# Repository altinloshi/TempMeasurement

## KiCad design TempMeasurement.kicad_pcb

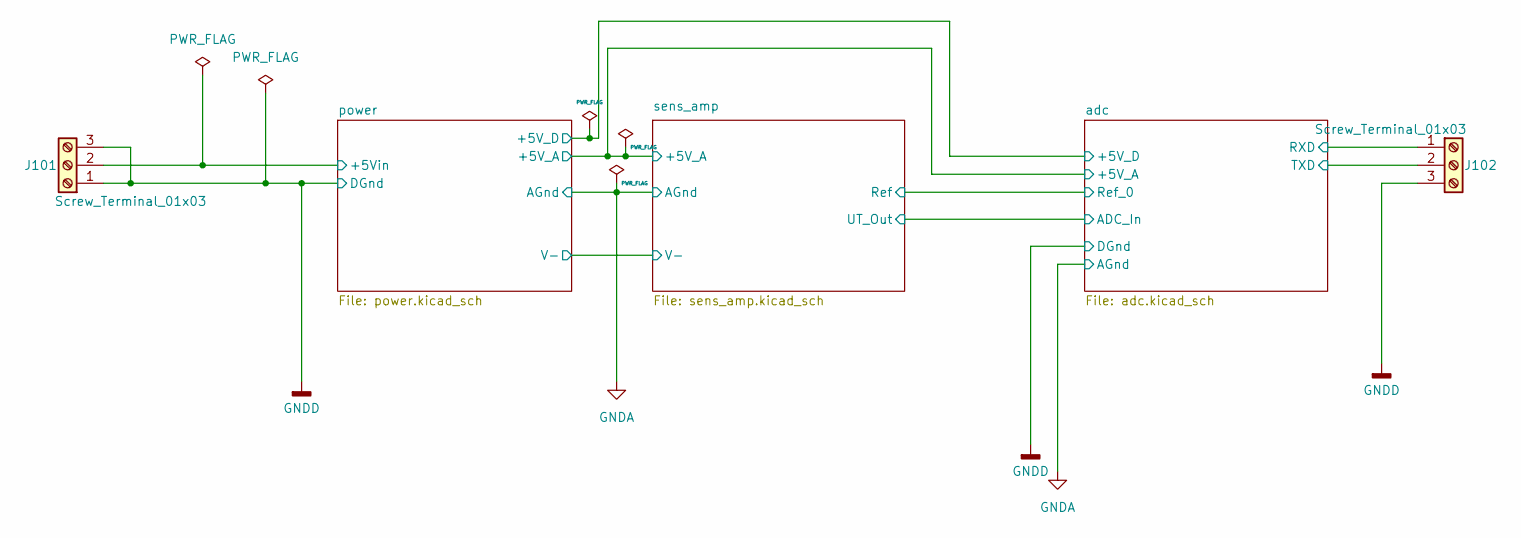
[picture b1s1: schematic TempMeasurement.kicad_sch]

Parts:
J101, J102: Screw_Terminal_01x03; TerminalBlock_Phoenix_MPT-0,5-3-2.54_1x03_P2.54mm_Horizontal

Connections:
/adc/RXD: J102.1; also elsewhere on the board
/adc/TXD: J102.2; also elsewhere on the board
/power/+5Vin: J101.2; also elsewhere on the board
GNDD: J101.1, J101.3, J102.3; also elsewhere on the board

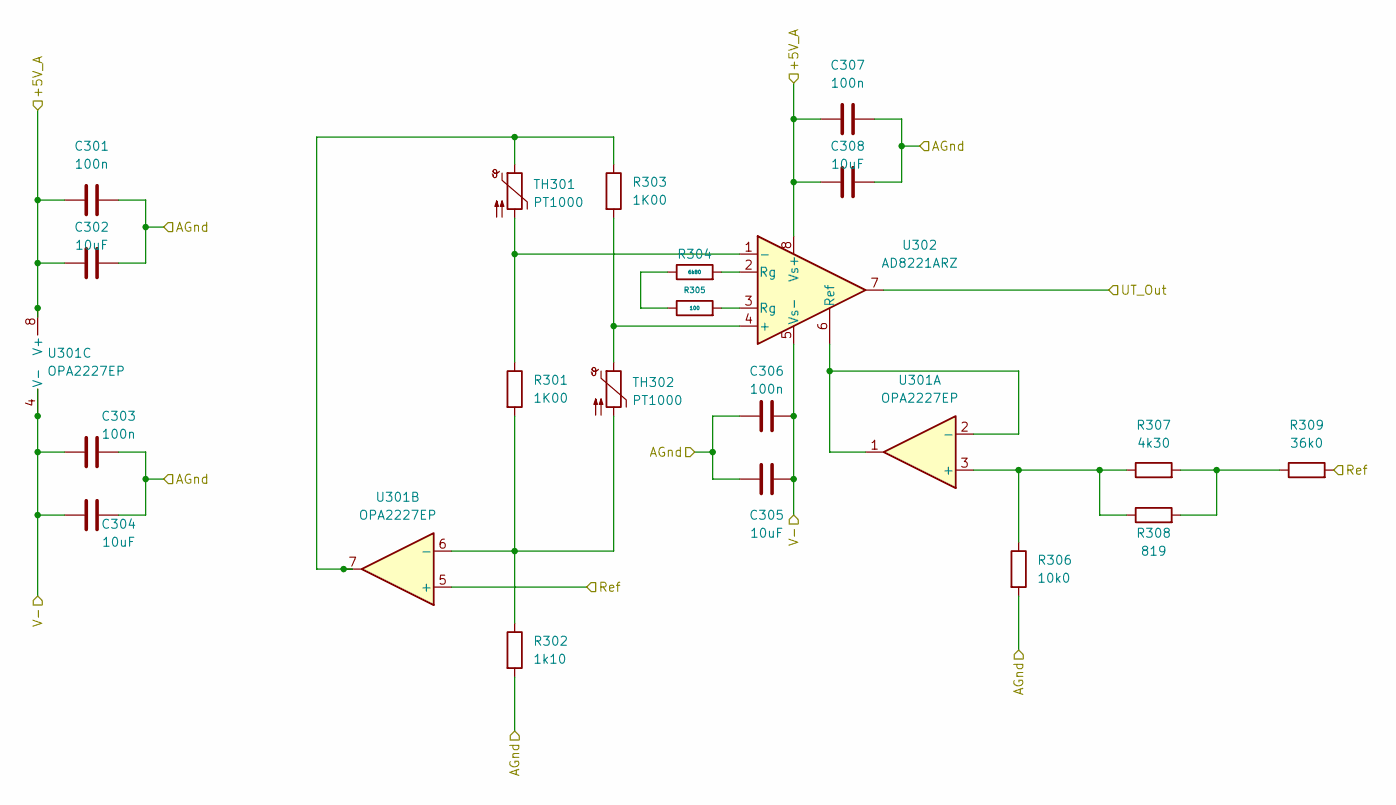
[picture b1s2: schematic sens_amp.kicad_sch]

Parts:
C301, C303, C305, C307: 100n; C_0805_2012Metric
C302, C304, C306, C308: 10uF; C_0805_2012Metric
R301, R303: 1K00; R_0805_2012Metric
R302: 1k10; R_0805_2012Metric
R304: 6k80; R_0805_2012Metric
R305: 100; R_0805_2012Metric
R306: 10k0; R_0805_2012Metric
R307: 4k30; R_0805_2012Metric
R308: 819; R_0805_2012Metric
R309: 36k0; R_0805_2012Metric
TH301, TH302: PT1000; R_0805_2012Metric
U301: OPA2227EP; SOIC-8_3.9x4.9mm_P1.27mm
U302: AD8221ARZ; SOIC-8_3.9x4.9mm_P1.27mm

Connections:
/adc/+5V_A: C301.1, C302.1, C307.1, C308.1, U301.8 (V+), U302.8 (Vs+); also elsewhere on the board
/adc/ADC_In: U302.7; also elsewhere on the board
/adc/Ref_0: R309.2, U301.5 (+); also elsewhere on the board
/power/V-: C303.1, C304.1, C305.1, C306.1, U301.4 (V-), U302.5 (Vs-); also elsewhere on the board
GNDA: C301.2, C302.2, C303.2, C304.2, C305.2, C306.2, C307.2, C308.2, R302.2, R306.2; also elsewhere on the board
unnamed: R303.1, TH301.1, U301.7
unnamed: R304.1, R305.1
unnamed: R304.2, U302.2 (Rg)
unnamed: R305.2, U302.3 (Rg)
unnamed: R307.2, R308.2, R309.1
unnamed: R306.1, R307.1, R308.1, U301.3 (+)
unnamed: U301.1, U301.2 (-), U302.6 (Ref)
unnamed: R301.2, R302.1, TH302.2, U301.6 (-)
unnamed: R303.2, TH302.1, U302.4 (+)
unnamed: R301.1, TH301.2, U302.1 (-)

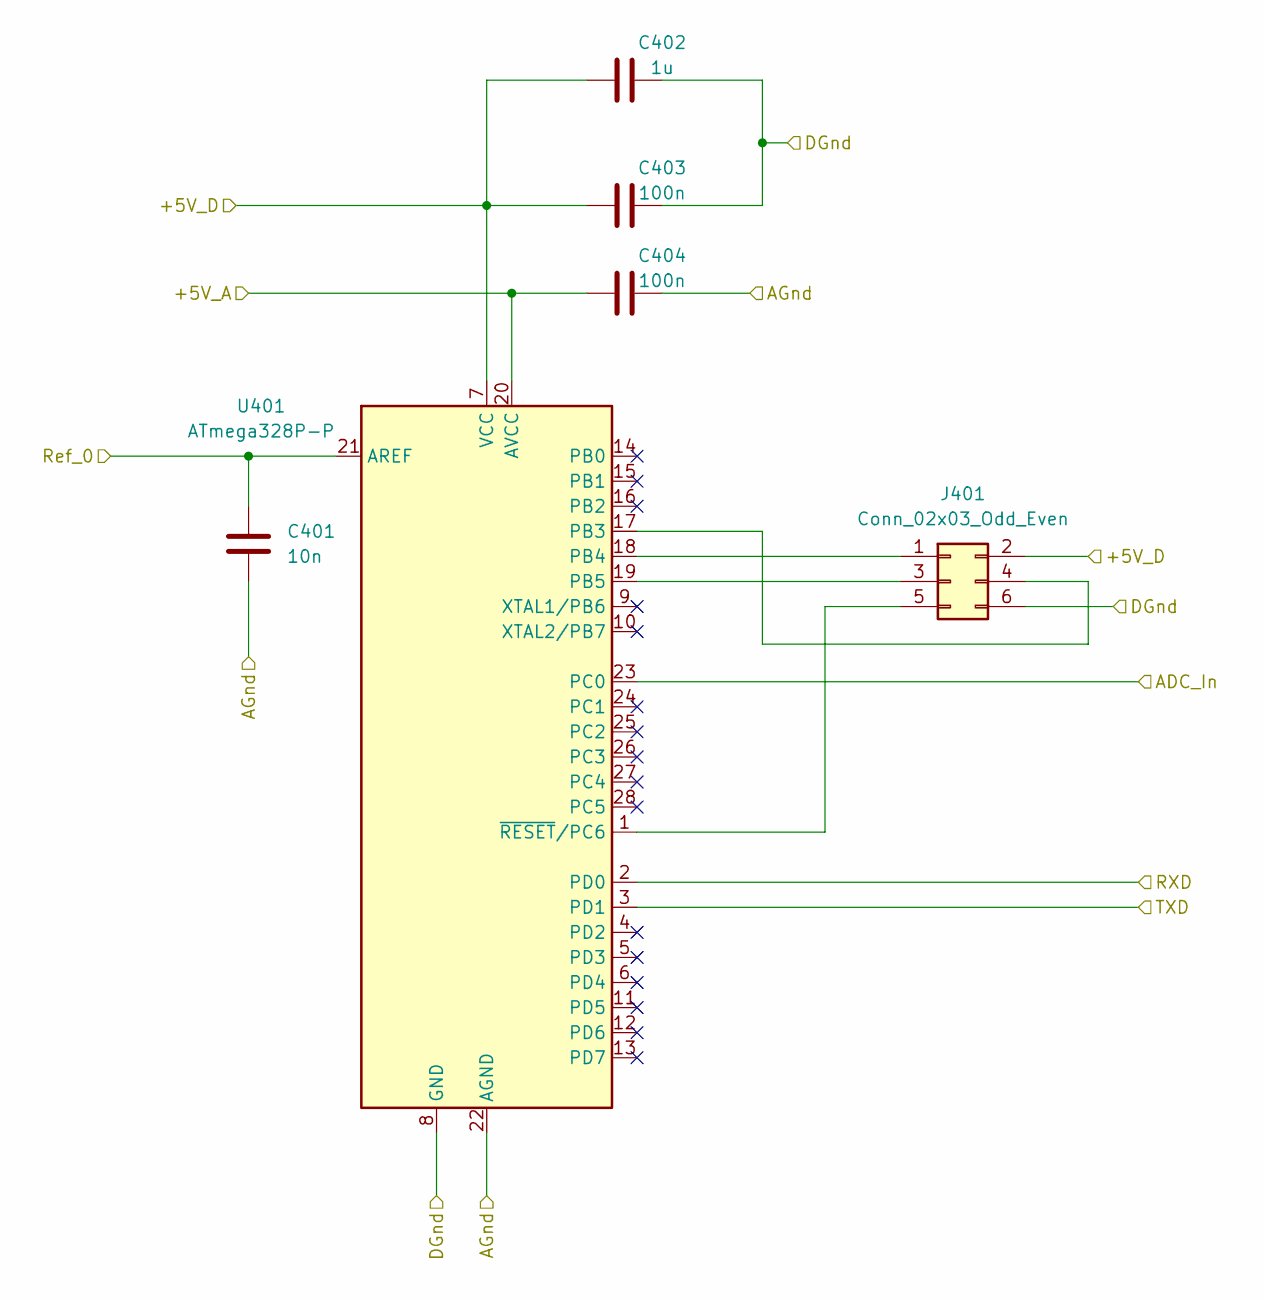
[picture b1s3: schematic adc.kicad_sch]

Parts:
C401: 10n; C_0805_2012Metric
C402: 1u; C_0805_2012Metric
C403, C404: 100n; C_0805_2012Metric
J401: Conn_02x03_Odd_Even; PinHeader_2x03_P2.54mm_Vertical
U401: ATmega328P-P; DIP-28_W7.62mm

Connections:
/adc/+5V_A: C404.1, U401.20 (AVCC); also elsewhere on the board
/adc/+5V_D: C402.1, C403.1, J401.2, U401.7 (VCC); also elsewhere on the board
/adc/ADC_In: U401.23 (PC0); also elsewhere on the board
/adc/RXD: U401.2 (PD0); also elsewhere on the board
/adc/Ref_0: C401.1, U401.21 (AREF); also elsewhere on the board
/adc/TXD: U401.3 (PD1); also elsewhere on the board
GNDA: C401.2, C404.2, U401.22 (AGND); also elsewhere on the board
GNDD: C402.2, C403.2, J401.6, U401.8 (GND); also elsewhere on the board
unnamed: J401.1, U401.18 (PB4)
unnamed: J401.3, U401.19 (PB5)
unnamed: J401.4, U401.17 (PB3)
unnamed: J401.5, U401.1 (~RESET/PC6)

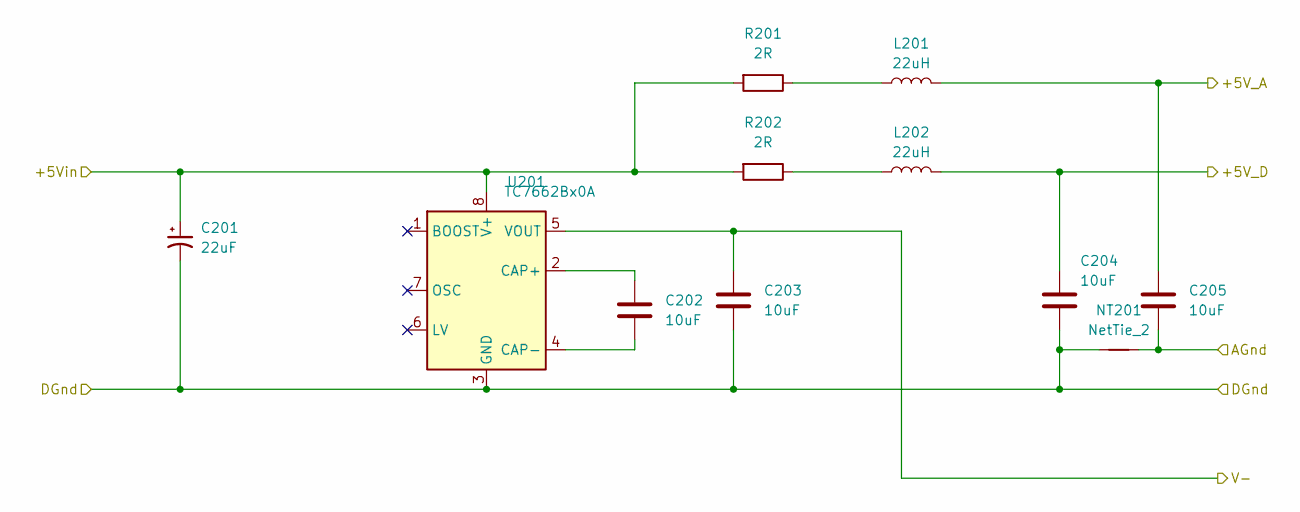
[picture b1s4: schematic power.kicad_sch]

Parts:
C201: 22uF; CP_EIA-7343-15_Kemet-W
C202, C203, C204, C205: 10uF; C_0805_2012Metric
L201, L202: 22uH; L_0805_2012Metric
NT201: NetTie_2; NetTie-2_SMD_Pad2.0mm
R201, R202: 2R; R_0805_2012Metric
U201: TC7662Bx0A; SOIC-8_3.9x4.9mm_P1.27mm

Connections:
/adc/+5V_A: C205.1, L201.2; also elsewhere on the board
/adc/+5V_D: C204.1, L202.2; also elsewhere on the board
/power/+5Vin: C201.1, R201.2, R202.2, U201.8 (V+); also elsewhere on the board
/power/V-: C203.1, U201.5 (VOUT); also elsewhere on the board
GNDA: C205.2, NT201.2; also elsewhere on the board
GNDD: C201.2, C203.2, C204.2, NT201.1, U201.3 (GND); also elsewhere on the board
unnamed: L201.1, R201.1
unnamed: L202.1, R202.1
unnamed: C202.1, U201.2 (CAP+)
unnamed: C202.2, U201.4 (CAP-)

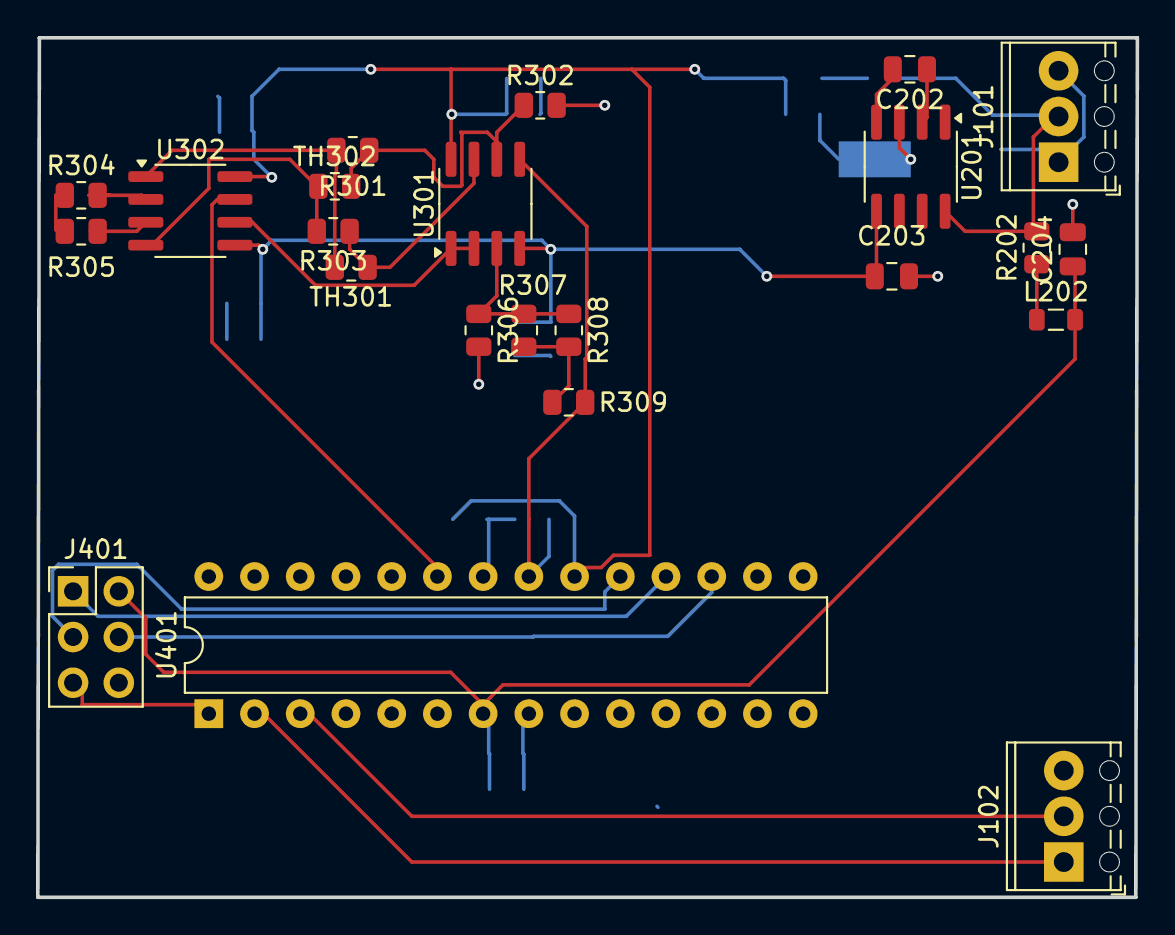
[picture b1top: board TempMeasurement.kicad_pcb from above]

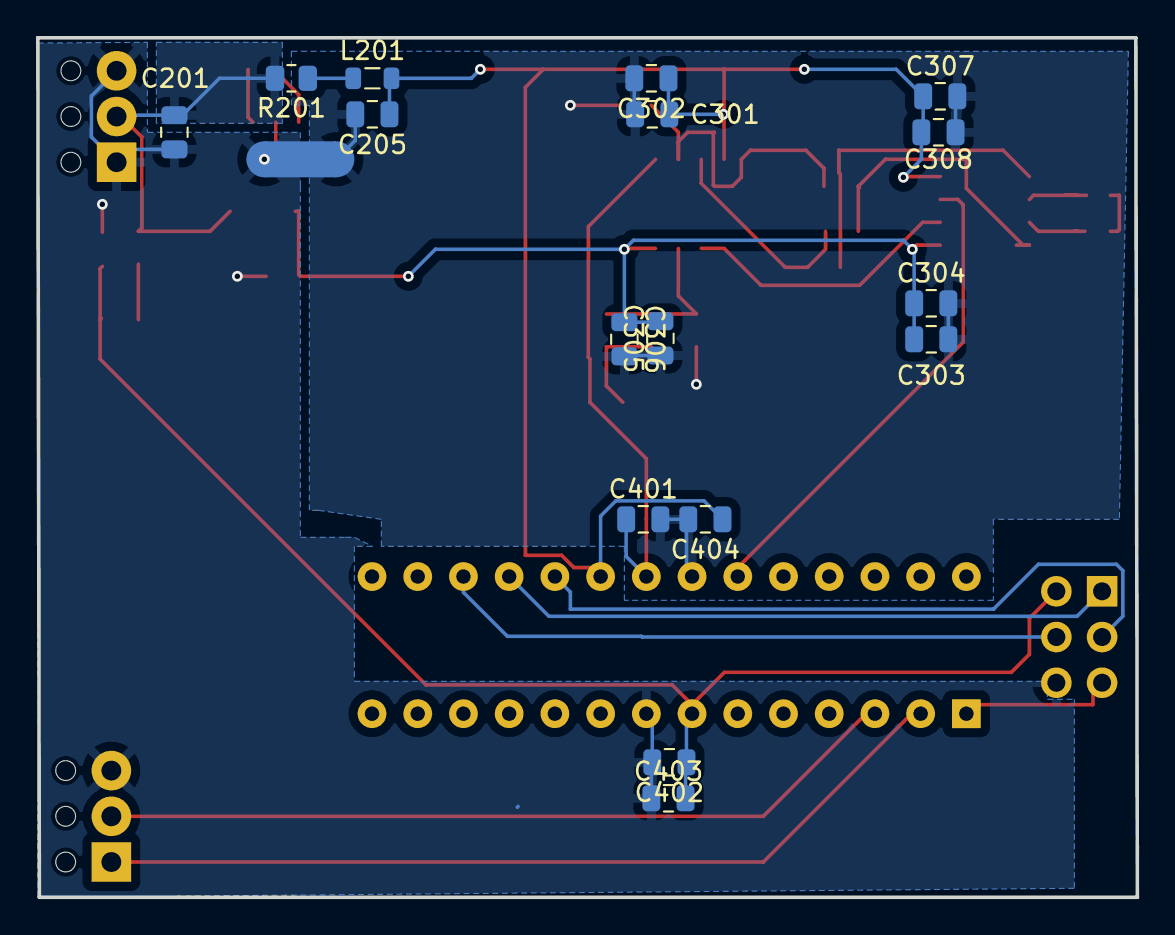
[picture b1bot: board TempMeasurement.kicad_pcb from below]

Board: 2 copper layers, 61.1 x 47.8 mm, 40 parts (17 on the bottom side), 28 nets.
